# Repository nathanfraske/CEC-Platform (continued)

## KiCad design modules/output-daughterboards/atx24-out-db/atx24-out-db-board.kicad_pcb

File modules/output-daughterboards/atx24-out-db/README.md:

# 24-pin ATX output daughterboard — BETA-1

Passive connector-daughterboard for the 24-pin ATX module's OUTPUT side, per
spec **§2.8 v1.4.0** (`CEC-Platform-Ground-Truth-Spec.md`) and the owner
ruling `docs/standard-tier-review/SYNTHESIS-beta-plan.md` §D-5a. Mates with
the main board's `TB1`–`TB9` Keystone 3586 universal blade clips (TB symbols
exist in `modules/atx-24pin-rev3`'s **schematic**, commit `b76a62a`; **no
clip placement exists on any main-board PCB yet** — this board's tab grid is
the authoritative mating drawing, see "Keying") and reproduces the full
24-circuit ATX output pin map for a bare pigtail or a future MODDIY-class
vertical header. **No active or passive components** — connector bodies and
fan-out copper only, per the ratified "no components beyond the connector
body and its fan-out copper" text.

> **ITERATION 7 (2026-07-06, owner-ratified) — READ FIRST, supersedes the
> iteration-5 numbers below where they differ.** Main-board mate changed:
> Keystone **3557 clip → TE 63969-1 FASTON .250 PCB RECEPTACLE** (vertical/
> top entry; the DESIGNED mate for the 63951-1 blade — rev-E dwg note 3
> puts our 0.81 mm thickness at its design centre, retiring the
> 27%-over-centre fit item; 22.9 A @ 30 °C rise per TE 108-1706; 63968-1 =
> same-land low-insertion-force fallback; LCSC C2961150, stock ~5 =
> restock watch, DigiKey depth). **ORIENTATION (owner requirement, proven
> from `lib/datasheets/TE_63969_customer_drawing_revE.pdf` and
> checker-asserted):** the receptacle's two Ø1.40 holes at 5.08 mm pitch
> run **perpendicular to the row**, along the descending blade's plane —
> plan-congruent with the blade's own leg holes; the blade's bottom edge
> enters the slot edge-wise. Along-row footprint is therefore only the
> receptacle's ~3.7 mm across-thickness depth (UN-DIMENSIONED on rev E —
> **depth ≤ 4.0 mm is the #1 sample-gate item; above it, atx24 falls back
> to a 6.3 pitch**): pitch floor 3.7 + 0.5 = **4.2 mm**; pitches now
> **atx24 4.2 / eps 4.7 / pcie 5.2**. Joint counts re-ratified at
> 22.9 A/125% (18.32 A allowable per joint): **atx24 10 tabs** (3V3 gains a
> second joint at 24.0 A basis; GND ×4 = 18.0 A/joint = 127% hairline,
> surfaced), **eps holds 6/cable** (17.33 A = 132%), **pcie 6/cable**
> (3/polarity; 2/polarity was 19.5 A = 117% FAIL). Boards: **atx24 61.0 ×
> 21.4, eps 28.5 × 20.0, pcie 31.0 × 20.0 mm** (pcie GROWS — the +2
> ratified joints outweigh its pitch win; honest number). Seating: float
> 12.41 mm unchanged; the 8.38 mm receptacle top is cleared by **4.03 mm**;
> detent-hole engagement at nominal float is NOT established (retention may
> be spring-friction only — sample item, with gang insertion force). Full
> record: `docs/standard-tier-review/blade-fit-check-2026-07-04.md`
> **addenda 6–7**.

> **ITERATION 5 (2026-07-05, owner) — READ FIRST, supersedes the iteration-4
> numbers below where they differ.** Main-board clip part changed: Keystone
> **3586 (SMD) → 3557 bare top-entry clip** (THT, UL 30 A @ 500 V AC; the
> "3557-2" this repo vendored earlier is the 2-in-1 HOUSED holder, a
> different product — naming corrected; 3586 stays vendored as the SMD
> fallback). Clip rotated slot-perpendicular-to-wall; its **leg pair runs
> ALONG the row** (verified from the catalog mounting details — this
> contradicts the leg-parallel-to-jaw assumption and caps the win): pitch
> floor = 3.4 leg pitch + 2.4 pad + 0.5 solder web = **6.3 mm**, pitches now
> **atx24 6.3 / eps 6.7 / pcie 7.2** (keying margins 1.00/0.75/1.35, teeth
> re-verified). Boards: **atx24 69.5 × 21.4, eps 38.5 × 20.0, pcie 26.6 ×
> 20.0 mm**. Seating: uniform 4.34 mm leg row, float 12.41 mm at 1.0 mm tip
> clearance; the taller 10.2 mm clip's top is cleared by 2.21 mm; engagement
> now spans the clip's full interior. atx24 also swaps its signal stub: the
> 2×5 header is RETIRED for a **1×4 right-angle blind-mate pin header**
> (long-tail Dupont class, pins down past the edge parallel to the blades,
> single-motion drop-in; NEW pin map 1=−12V, 2=PS_ON#, 3=PWR_OK, 4=GND) plus
> **six DNP sense-return pads SR1–SR6** (OQ-88 provision form only). #1
> fit-check item: the 0.81 mm FASTON tab is ~27% over the clip's 0.64 mm
> fuse-blade design centre (inside the published .020–.032 acceptance, at
> its ceiling — stiffer grip expected, sample-gated). Full record:
> `docs/standard-tier-review/blade-fit-check-2026-07-04.md` **addendum 5**.

DRAFT (no fab yet — the OQ-86 physical fit-check sample gate is still open).

## Posture — vertical card, tabs blade-DOWN (owner sketch, 2026-07-05)

This board is a small vertical card standing perpendicular to the main board
(owner ruling 2026-07-04/05, unchanged). The connector form went through
three same-day iterations on 2026-07-05 and is settled by the **owner's
sketch** (the final ruling; the two earlier forms — TE 63849-1
straight-tab/side-entry, then a mis-modeled "blade hangs past the edge
in-plane" reading of the 63951-1 — are retired, record in
`docs/standard-tier-review/blade-fit-check-2026-07-04.md` addendum 3):

The tabs are **TE 63951-1** (RIGHT-ANGLE FASTON .250 — "the blade that has
the 90 degree rotation in it," owner). The part is a flat in-plane **L
stamping**: the blade runs along the leg-pitch axis past the blade-side leg,
standing **2.54–8.89 mm off its seating face** (TE dwg C=63951 rev L2,
`lib/datasheets/TE_63951-1.pdf`). Mounted per the sketch: the two legs go
**horizontally** through this board's face, the 5.08 mm leg pitch runs
**vertically** (legs stacked one above the other), and the blade therefore
points **straight down**, descending past this board's bottom edge at the
2.54–8.89 mm Z-standoff — *"It needs to align vertically so it can actually
point down and slot into the clip."* The whole assembly drops vertically;
each blade enters its main-board Keystone 3586 clip's **top-entry** jaws
broadside (the clip's native auto-blade-fuse mode, Keystone dwg 3586). The
board's own bottom edge **floats clear of the main board** — *"the TAB does
the reaching down, not the board"* — no board material or copper crosses
Edge.Cuts; only the tab's off-board descender passes below the edge level,
offset from the board plane with no conflict.

**Board axes**: X = length (FREE dimension, minimized opportunistically);
Y = height. **The ≤15 mm height cap is EXPLICITLY RELAXED by the owner for
the iteration-4 compact form** (owner follow-up on the 145 mm iteration-3
board: *"Good lord those are long, can the agent stack the blades right
next to each other and put them below the pinout? That should tell us how
tall these are really going to be"*) — the deliverable is the honest
minimum height of the two-band stack.

**Measured final size**: **69.5 × 21.4 mm** (length × height). The tab row
returned BELOW the field (two-band stack: field + corridor on top, packed
tab row underneath), halving the length (145.1 → 72.8 mm) at a true height
cost of 13.6 → 21.4 mm. Height decomposition (all measured constants):
0.4 top margin + 10.2 field + 0.1 gap + 2.25 corridor (4 In2 lanes) +
0.3 lane-to-pad clearance + 7.58 tab pad band (2 × 3.79) + 0.55 edge
margin. Length is now tab-row-driven (9 × 8.4 mm + margins ≈ 73, just over
the field+header band's ~68).

## Mating geometry / seating model (iteration-4 numbers)

All numbers from `scripts/gen-output-daughterboard.py seating_report()` and
the two vendored drawings; the seating invariant is now the leg-row height
ABOVE THE BOTTOM EDGE, **uniform across all three families** (the tab band
is the lowest thing on every board; asserted by the check script):

- **Leg row** (leg-pair midpoint): **4.34 mm above the bottom edge**
  (= 3.79 pad extent + 0.55 edge margin; the lower pad's copper clears the
  board's 0.5 mm copper-to-edge constraint by 0.05 mm — sized off the
  iteration-3 `copper_edge_clearance` lesson, asserted by the checker).
- **Blade standoff** (unchanged): descender hangs 2.54–8.89 mm off the
  front face; main-board **clip slot centreline at 5.72 mm** from the wall
  plane, slot axis PERPENDICULAR to the wall line; blade width 6.35 mm vs.
  the clip's rated ≤6.4 mm accepted-tab range; slot opening 1.57 mm vs.
  0.77–0.83 mm blade thickness — ~2× clearance.
- **Descender reach**: blade tip 15.75 mm below the leg row (drawing-derived
  chain dim, flagged in the footprint descr) → the tip descends **11.41 mm
  below the bottom-edge level** — uniform across families now, off-board at
  the Z-standoff.
- **Seating**: the board **cannot and does not edge-rest** — it floats,
  hanging on the clip grip (+ chassis strain relief, OQ-87). At the
  recommended **1.0 mm tip clearance** above the main-board surface (hard
  stop ≈0.4–0.5 mm when the tip meets the clip's own SMT base metal), the
  bottom edge floats **12.41 mm** above the main board — now UNIFORM across
  all three families (the invariant moved from iteration-3's "uniform
  top-edge height" to "uniform float" when the tab band became
  bottom-pinned); this board's top edge sits **33.8 mm** above the main
  board (eps/pcie: 32.4 mm). The compact form trades assembly stack height
  for board length — reported, not hidden. **Engagement** unchanged: the
  blade spans the clip's full 7.16 mm interior from the tip clearance up
  and protrudes fuse-like above the clip top. Legs protrude 2.21 mm out
  the back face (3.81 mm legs − 1.6 mm board); keep that clear behind the
  wall.

## Mounting / retention — no mounting holes (owner directive, 2026-07-05)

Earlier drafts of this pass carried 4× M3 corner mounts; the owner cut them:
*"they don't need a ton of mounting holes either... that can probably go
away."* Retention is instead:
1. The Keystone 3586 clip's own **high insertion force** — a deliberate
   **feature**, not a shortfall, per the owner's 2026-07-04 ruling on this
   connector family: these joints are not meant for casual swapping, and
   mis-seat/pull-out (which hardware would be there to prevent) is exactly
   the failure a stiff joint rejects.
2. **Chassis strain relief** on the cable/assembly side (spec §2.8 v1.4.0);
   OQ-87 still owns the numeric pull-force/flex-cycle spec for that
   interface.
No footprint or BOM line changed because of this — mounts were never a
schematic/BOM part on this generator (PCB-only mechanical footprints), so
removing them only touched the PCB placement code.

## Tab map (9 joints, TE 63951-1 / LCSC C591344)

| Ref | Net | ATX pins bundled | Matches main-board clip |
|---|---|---|---|
| J10 | +12V | 10, 11 | TB1 |
| J11 | +5V | (shares +5V net with J12) | TB2 |
| J12 | +5V | 4, 6, 21, 22, 23 | TB3 |
| J13 | +3V3 | 1, 2, 12, 13 | TB4 |
| J14 | +5VSB | 9 | TB5 |
| J15–J18 | GND | 3, 5, 7, 15, 17, 18, 19, 24 | TB6–TB9 |

Joint count and per-rail split (12V×1, 5V×2, 3.3V×1, 5VSB×1, GND×4) are the
spec-ratified §2.8 v1.4.0 numbers, and the tab ORDER (12V, 5V, 5V, 3.3V,
5VSB, GND×4) matches the already-built main board's `TB1`–`TB9` net sequence
1:1 — verified against `modules/atx-24pin-rev3/README.md`.

## Signal header (J20, 2×5 2.54 mm, `cec:CEC_CONN_2x5`)

Pin order matches the main board's `J_SIG` (same commit) exactly, so a
mating cable/header is not left to guess a 1↔2 swap:

| Pin | Net | Note |
|---|---|---|
| 1 | PS_ON# | |
| 2 | PWR_OK | |
| 3 | −12V | |
| 4 | GND | local reference |
| 5–10 | reserved | no-connect; sense-return provision (OQ-88), unpopulated |

No 5VSB-sense/remote-sense net exists on the main board's signal set today
(verified against the current netlist per that board's own README), so none
is carried here either.

## Output field (J1, `cec-Connector_Generic:ATX24_Daughterboard_Field_P4.20mm`)

Bare THT solder field, 24 positions, 2×12 @ 4.20 mm pitch / 5.5 mm row —
geometry measured off the vendored, verified Molex Mini-Fit Jr 5569-24A1
land (`lib/vendor/Connector_Molex.pretty`), same pitch family the study's §4
recommends for exactly this field. Reuses the platform's own `cec:CEC_ATX_24`
symbol (same pin names/map as J3 on the 24-pin module) so the electrical
identity is inherited verbatim; only the footprint differs — a bare pad
field, no male-header shroud. 20 of the 24 positions are power-class (1.8 mm
drill / 2.7×3.7 mm oval, the real Molex land, 16 AWG-class); the 4 non-power
ATX circuits (pin 8 PWR_OK, pin 14 −12V, pin 16 PS_ON#, pin 20 NC/reserved)
are downsized to 1.4 mm drill / 2.6 mm round (18 AWG-class, matching the TE
tab's own leg size).

**Population options** (same field serves all three, per the study §4 "one
field, two/three uses"):
1. **Bare pigtail** (default) — hand-solder 16 AWG (power) / 18 AWG (signal)
   wire directly into the field.
2. **MODDIY-class vertical female header** — dimensionally compatible
   (4.20 mm pitch, same "Molex 5557/5559 family" pitch the part claims), but
   **NOT placed here**: no MODDIY footprint is vendored in this library (no
   manufacturer name / MPN / datasheet — OQ-88's provenance gap), so nothing
   is invented. On the standing-board posture the header's own pins point
   horizontally (same direction as the tabs), so — unlike an earlier,
   since-corrected concern about a parallel-mezzanine framing — there is no
   height-budget conflict with a vertical header option here; population
   stays an owner decision pending the physical fit check (OQ-86/88).
3. **Sellable daughterboard-plus-extension assembly** — same holes, wire
   soldered in with a chassis-anchored strain-relief bar, terminating in a
   standard female housing (OQ-89, SKU TBD). Wire dress runs parallel to the
   main board (the natural consequence of the field's pins exiting
   perpendicular to a *standing* board — i.e. horizontally).

## Keying

**Single row of 9 tabs at 8.9 mm pitch** (mm centre-to-centre), net order
unchanged from the original design (12V, 5V, 5V, 3.3V, 5VSB, GND×4) — see
the tab map above. Under the sketch model the pitch floor is no longer the
tab body at all (each tab is only ~0.84 mm thin along the row, stamping
plane perpendicular to the face; its 2.5 mm pads are its widest row-axis
feature → tab-to-tab pad gap 5.9 mm — trivially clear). The binding floor
is the **main-board clip row**: the Keystone 3586 rotated per the sketch
(slot axis perpendicular to the wall) presents its narrow dimension along
the row — 3.81 mm body / 3.82 mm courtyard (measured off the vendored
footprint; Keystone dwg 3586 `.150 in`) and — the real driver — a
**6.60 mm SMD pad span**. **Pitch floor = 6.60 + 0.50 stated adjacent-clip
solder/paste clearance = 7.10 mm** (iteration-4 packed row, owner: "stack
the blades right next to each other"). This board sits at **8.4 mm** —
above the floor for a ROUTING reason, not slack: 8.4 = 4 × 2.1 mm, the
field-stub lattice period (4.2 mm ATX columns + the +2.1 mm dodge), and
`pcb_placement()` grid-aligns the row's x0 to lattice + 1.05 mm, so every
tab stub/via in the shared corridor X-range clears every field stub/via by
≥1.05 mm against a ~0.7 mm conflict radius (at any non-multiple pitch the
9 tabs' lattice offsets provably sweep the full 2.1 mm cycle and some tab
always lands in conflict). At 8.4 mm: **4.58 mm clip body gap, 1.80 mm pad
gap** — asserted with printed numbers by `check_output_daughterboards.py`
§3b.

**The real safety property is proved, not assumed.**
`scripts/check_output_daughterboards.py` computes every family's tab-centre
list from its own `pcb_placement()` (the exact coordinates on the committed
board) and, for every ORDERED pair of families, searches all 4 rotations
(0/90/180/270°) × every candidate translation for a rigid mapping that seats
one family's whole tab set onto a subset of another's, within 0.5 mm
(bipartite exact-match, not a coincidence heuristic) — see that script for
the algorithm. All 6 ordered pairs come back "cannot seat" — **re-proved at
the iteration-4 packed pitches (8.4/7.6/7.1)**, whose keying margins are
(G/2)×Δpitch: pcie-in-eps 0.75 mm, pcie-in-atx24 1.95 mm, eps-in-atx24
2.00 mm — all ≥1.5× the 0.5 mm tolerance, so **pitch differentiation
survives at the packed floor and no pattern keying (offset tab /
asymmetric skip) was needed**. The historic failure mode stays live in the
checker's teeth: an earlier set (8.6/8.3/8.2) MEASURABLY seated PCIe's 4
tabs inside EPS's grid at only 0.15 mm end error, and a sabotaged 7.2 mm
EPS pitch (Δ0.1 from pcie's 7.1) was re-verified this pass to make the
proof correctly FAIL. See `scripts/gen-output-daughterboard.py`'s
`TAB_PITCH` comment for the full floor + delta math. **This
daughterboard's tab grid is the authoritative main-board mating drawing** —
the four main boards carry TB clip SYMBOLS in their schematics only (no PCB
placement exists on this branch), so the future main-board clip-placement
pass mirrors these exact X positions, the rotated-clip orientation, and the
5.72 mm slot-centreline standoff from the wall plane.

**Dual-face tabs**: evaluated and REJECTED under the earlier flat-tab model
(cross-face interleaving relieved only pad-to-pad clearance, ~11 %, not the
assumed ~50 % — full math retained in this section's git history). Under
the sketch model the question is moot a fortiori: the row pitch is
clip-limited and keying-limited, not tab-body-limited (each tab is ~0.84 mm
thin along the row), so a second face would buy nothing. Single-face,
single-row stands.

## Layer stack / routing

**4-layer** (F.Cu / In1.Cu / In2.Cu / B.Cu, 2 oz outer / 1 oz inner — the
platform's own interposer convention). GND floods **In1.Cu alone**, a
single full-board plane (the largest, most-scattered net; GND tabs and GND
field pins connect through it with zero explicit tracks). Of the remaining
7 nets, only **4 are real multi-point busses** — +12V, +5V, +3V3, +5VSB
(several field pins, one or two tabs each) — and only THOSE get a lane. The
other 3 (−12V, PWR_OK, PS_ON#) are a plain 2-terminal net apiece (exactly
one field pin to the matching `J20` header pin, no tab at all,
netlist-verified), so they route as direct point-to-point tracks with no
lane at all — see the two design notes below.

**The 4 BUS lanes live in a short CORRIDOR** below the field's bottom row,
on **In2.Cu only** — 4 thin zones (0.3 mm wide, 0.65 mm pitch) spanning the
full board width. Each bus field-pin runs a 0.5 mm F.Cu stub down to its
own lane + a 0.3/0.5 mm via (smaller than this platform's usual 0.5/0.9 mm
power via — the 0.65 mm slot pitch cannot safely hold a 0.9 mm via without
adjacent slots' vias overlapping). Each rail TAB — now in the packed row
BELOW the corridor (iteration-4 two-band stack), legs stacked vertically —
bridges its two leg pads (both numbered "1" but with no internal copper
between them in the footprint) with a vertical 0.5 mm F.Cu track, plus an
up-stub from the UPPER leg into its own lane + the same 0.3/0.5 mm via.
The tab row shares the corridor's X-range with the field's own stubs/vias,
which is exactly what the 8.4 mm grid-aligned pitch solves (see "Keying"):
every tab stub/via sits 1.05 mm off the field-stub lattice. The tab pads'
own In2 anti-pads stay 0.3 mm clear of the deepest lane band by placement
(`_LANE_PAD_CLR` — deliberately above the 0.2 mm zone clearance so the
fill never sits at exact tangency with a pad anti-pad); the via sits at
its own lane's centreline, clearing the 0.65 mm-pitch neighbours by the
same measured 0.25 mm the field vias rely on. The board's bottom margin
below the tab pads is 0.55 mm (0.5 mm board copper-to-edge constraint +
0.05 slack — the iteration-3 `copper_edge_clearance` lesson applied up
front), which is what the 21.4 mm height lands on.

**DESIGN NOTE — a two-layer lane split does NOT help here, though it looks
like it should** (a first pass built one, then reverted it once DRC caught
the result). Splitting the 4 (or originally, all 7) lanes across In2.Cu
*and* B.Cu, thinking two layers halve the stack depth, is unsafe for a
zone this thin: a via is a THROUGH feature, so a B.Cu-target via also
crosses In2.Cu at that (x,y), and KiCad's `ZONE_FILLER` auto-clears
(anti-pads) it there — normally harmless (exactly how a signal via safely
crosses a GND plane everywhere on this platform) *only* because a plane is
wide in both directions and copper can route around the hole. A 0.3 mm-tall
lane has no "around": a via whose keepout diameter (~0.9 mm here) exceeds
the lane's own height clears its FULL height at that one X, severing it
into two islands — measured as a real `unconnected_items` DRC hit between
two ends of what should obviously be one zone. Offsetting the two layers'
Y by half a pitch does not fix it either: the safe stand-off a via needs
from a foreign-LAYER lane it merely passes near
(`via_keepout_radius + lane_half_height + min_width`, ≈0.8 mm here) is the
same separation the lanes already need from EACH OTHER on one layer — two
layers buy nothing once every slot carries a via. The actual fix was fewer
lanes (drop the 3 point-to-point signals out of the scheme entirely), not
more layers.

**The 3 point-to-point signals (−12V/PWR_OK/PS_ON#) route on B.Cu**,
deliberately NOT F.Cu: the bus field-pins' dodge-then-descend stubs (below)
are on F.Cu and physically transit this same row-gap band on their way to
the corridor, at up to 12 different X's, so putting the point-to-point
runs on the otherwise-empty B.Cu avoids that whole family of crossings in
one move. No via is needed at either end (both the field pins and the
header pins are through-hole). The three runs still share one layer with
each other, so each gets its own dedicated Y inside the field's row-gap
(0.42 mm steps, a 0.2 mm track — thinner than the platform-default 0.4 mm,
because the safe row-gap window is only ~1.1 mm wide once the 0.25 mm
GND-class clearance and each pad's own 1.85 mm half-height are accounted
for), assigned by which row each signal approaches from so no two runs'
occupied (X, Y) actually coincide — worked out and commented in
`route_atx24()`, `scripts/gen-output-daughterboard.py`.

**Row-conflict fan-out rule** (why some bus field-pin stubs jog sideways):
the real ATX-24 pinout puts row0 (pins 1–12) and row1 (pins 13–24) on the
*same* 12 X-columns, so a straight vertical stub from a row0 pin can run
directly into a *different-net* row1 pad below it. Fixed by a **permanent
+2.1 mm (half the 4.20 mm pitch) sideways offset** on exactly the row0 pins
whose column-mate differs — landing dead-centre in the gap between two
adjacent pad columns (~0.75 mm clear of both neighbours) — taken for the
pin's *entire* descent (never jogged back), which also keeps every column's
own stub on a unique X for its whole length. Row1 pins and same-net columns
route straight down natively.

Field-pin currents here are modest (24-pin design basis: 6 A/circuit, ATX
bar) — 0.5 mm 2 oz stub tracks are comfortably inside that per-pin figure;
the per-rail AGGREGATE current (up to ~30 A on the 5V rail, per the study's
§1 margin table) is what the **9 blade-clip joints on the main board** are
sized for, not this daughterboard's own individual per-pin fan-out traces.
Verified DRC-clean (see below).

## Electrothermal sanity — PENDING (W-item, not wired this pass)

The repo's `cec_synth_pipeline.physics.electrothermal_solve` (IPC-2221 Picard
solver) is not parametrized for this board's "per-pin stub + thin lane"
topology; wiring it up is not cheap within this pass's scope. Hand sanity
only: 0.5 mm/2 oz external-layer traces at a 10 °C rise carry roughly 2–3 A
by the standard IPC-2221 external-trace curve — comfortably above the
~6 A/circuit-shared, sub-amp-per-stub currents these individual field-pin
fan-out traces actually see (the real per-rail current rides the 9 blade
joints, sized separately per the study). Flagged as a **pending W-item**:
run the real solver once it is generalized to this topology, before treating
this board as production-ready.

> **RESULT (2026-07-06, blade-interconnect thermal audit — the W-item above
> was executed): FAIL.** The four In2 bus lanes (0.3 mm × 1 oz) carry the
> full per-rail aggregates and are fusing-class at the design basis:
> DC-IR field solve = +5V 384 mV @ 30 A (11.5 W in the lane, J ≈ 2874 A/mm²),
> +12V 817 mV @ 12 A, +3V3 299 mV @ 24 A (9 % of the rail); the 2.5D coupled
> solve runs away (lane fuses). The hand sanity above sized the per-pin
> STUBS but the per-rail AGGREGATE crosses the lane between the tab group
> and the field pins (and ATX permits 6 A/pin, not "sub-amp"). Board fix =
> owner-gated regen (per-rail pour bands à la eps/pcie, or a widened 2 oz
> outer corridor). Full analysis:
> `docs/standard-tier-review/blade-interconnect-thermal-2026-07-06.md` (F1).

## Sense-return provision

Per spec §2.8 v1.4.0 / OQ-88: a zero-component sense-return contact (a
downstream voltage tap per sensed rail, feeding a main-board resistor divider
and spare ADC — mirrors Hub Standard's `MAIN_5V_SENSE`/`5VSB_SENSE` pattern)
is a candidate designed-in monitor for this joint's fretting-corrosion
wear-out mode. **Not decided** whether it ships, when, or at what
granularity — this board **provisions** for it only: 6 of the J20 header's
10 positions are reserved/no-connect, physically available for a future
sense-return tap without a board respin. No components are added here.

## Verification (this pass — 2026-07-05 iteration-4 compact two-band layout)

- ERC: 0 errors (5 benign `lib_symbol_mismatch` warnings, the same
  documented-benign class every generated schematic in this repo produces).
- Static connectivity audit (`scripts/audit-sch.py`): clean.
- DRC: **0 violations at error severity, 0 unconnected** (`kicad-cli pcb drc
  --severity-error`, and every `unconnected_items` slot is empty — the real
  gate `check_output_daughterboards.py` enforces). At full (all-severity)
  verbosity: 25 hits — 4 `silk_overlap` + 20 `silk_over_copper` (the
  documented-benign class) + 1 `silk_edge_clearance` (a single Value text
  near the bottom edge on the packed board — warning severity, no copper
  impact, same benign class as the platform's other boards carry). The
  iteration-3 `copper_edge_clearance` lesson (deepest copper vs the
  board's 0.5 mm edge constraint) is designed in up front this pass
  (`_TAB_EDGE_MARGIN` 0.55) — zero copper-edge hits on first regeneration.
- `scripts/check_output_daughterboards.py`: **all checks pass**, including
  the updated sketch-model checks (every tab rot 0 with legs stacked
  vertically at (0, ±2.54) re-parsed from the footprint file; the NEW
  uniform seating invariant — leg row 4.34 mm above the bottom edge on all
  three boards, lower pad clearing the 0.5 mm copper-to-edge constraint)
  and the §3b clip-fit assertions recomputed at the packed pitches (floors:
  0.5 mm pad gap = the stated solder clearance; 3.0 mm body gap). The
  geometric no-subset-seating proof re-ran at 8.4/7.6/7.1. Teeth
  re-verified at the packed floor: a sabotaged 7.2 mm EPS pitch (Δ0.1 from
  pcie's 7.1) makes the proof correctly FAIL (PCIe seats as a subset) —
  the same failure mode as the historic 8.3/8.2 incident.
- Netlist-verified: every one of the 9 tabs lands on its mapped ATX rail;
  every header pin lands on its mapped signal/GND/reserved net; the field's
  24 positions reproduce the standard ATX-24 map exactly (pin 20 = NC).
  Net-group identity vs. the pre-rework baseline confirmed (15→15 groups,
  0 missing/extra/renamed).

## Library assets used / added this pass

- **`cec-vendor:TE_63951-1_FASTON_Tab` / `cec-Connector_Blade:TE_63951-1_FASTON_Tab_250x032_RA_THT`
  (LCSC C591344, in stock, $0.099–$0.164/unit by qty)** — the right-angle
  .250 FASTON tab, footprint REWRITTEN this pass to the true in-plane-L
  geometry (legs at (0, ±2.54) stacked vertically, blade descending +Y past
  the board edge at the 2.54–8.89 mm standoff; thin projection-band
  courtyard/fab incl. the below-edge descender, drawn honestly) from TE's
  own customer drawing C=63951 rev L2 (`lib/datasheets/TE_63951-1.pdf`).
  The pass's first footprint modeled the L wrongly (blade perpendicular to
  the leg row, hanging past the edge in-plane) — retired by the owner's
  sketch; see `docs/standard-tier-review/blade-fit-check-2026-07-04.md`
  addendum 3.
- `cec-vendor:TE_63849-1_FASTON_Tab` / `cec-Connector_Blade:TE_63849-1_FASTON_Tab_250x032_THT`
  — pre-existing, LCSC C86469, **unreferenced by this generator** (left
  vendored; harmless).
- `cec:CEC_ATX_24` (pre-existing, reused verbatim for the field connector's electrical identity).
- `cec:CEC_CONN_2x5` + `cec-Connector_PinHeader_2.54mm:PinHeader_2x05_P2.54mm_Vertical` (pre-existing from the main-board task; this project's own library-asset pass independently reproduced byte-identical geometry).
- `cec-Connector_Generic:ATX24_Daughterboard_Field_P4.20mm` (this family's
  own field footprint; its Y-margin was tightened in an earlier pass —
  `scripts/gen-daughterboard-libassets.py`'s `solder_field()` now uses actual
  pad half-height instead of half the row pitch, dropping the field's own
  courtyard height 13.0→10.2 mm, the single biggest lever in fitting this
  board under the height cap — see that script for the reasoning).
  Unchanged this pass.
- No mounting-hole footprint — removed in an earlier pass (owner directive;
  see "Mounting / retention" above). Never a schematic/BOM part on this
  generator, so the BOM is unaffected.

Generator: `scripts/gen-output-daughterboard.py atx24-out-db`.

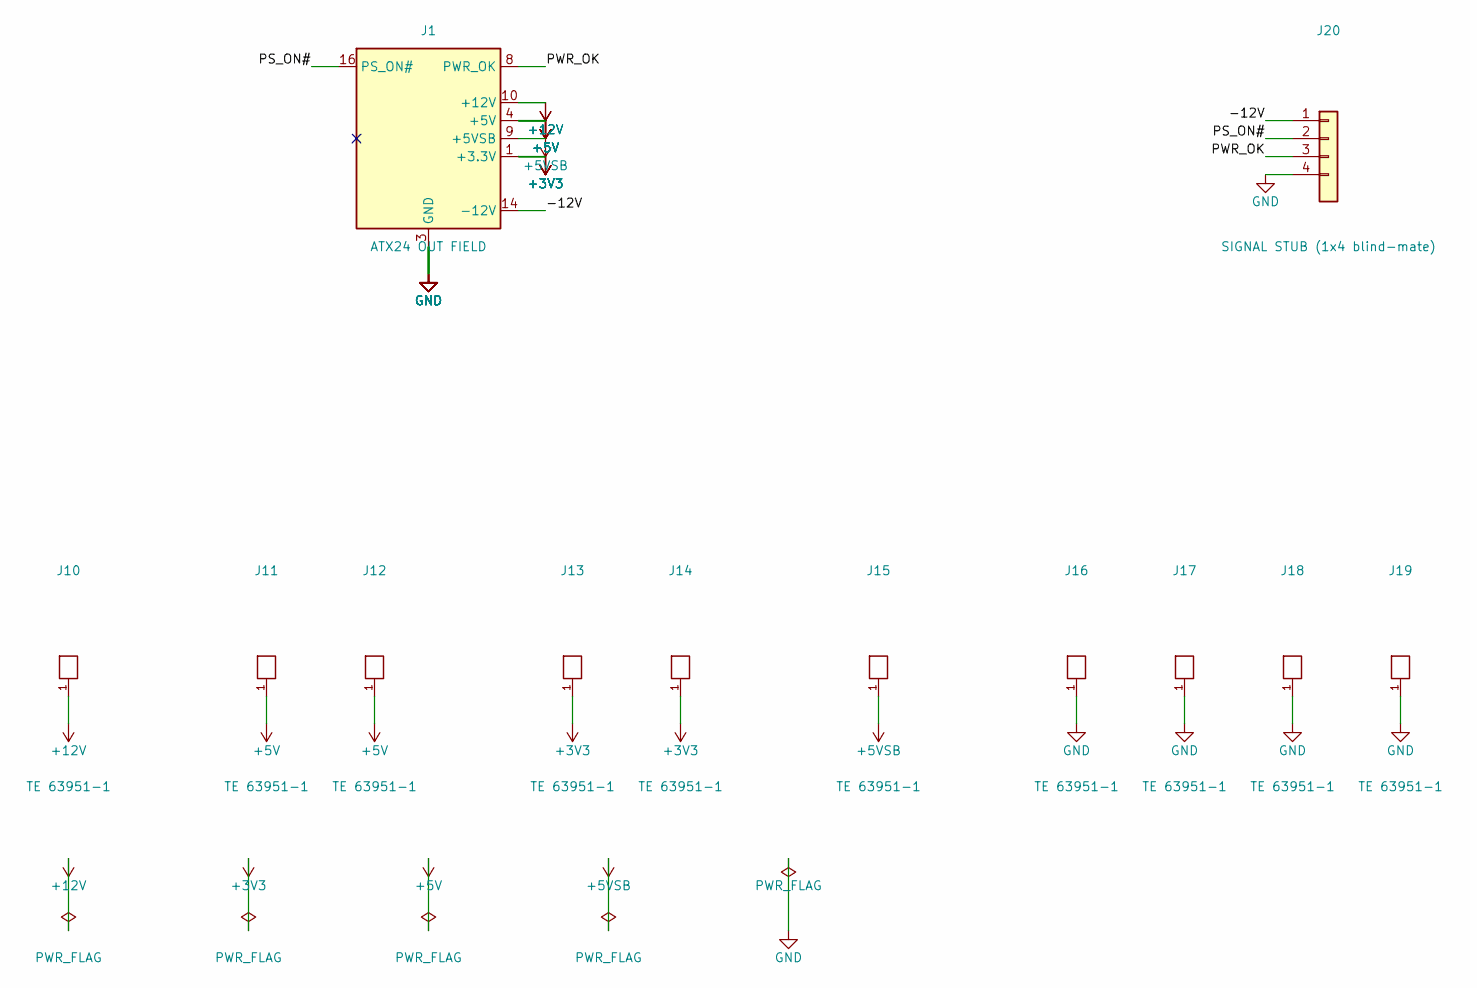
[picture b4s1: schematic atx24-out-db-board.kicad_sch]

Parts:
J1: ATX24 OUT FIELD; ATX24_Daughterboard_Field_P4.20mm
J10, J11, J12, J13, J14, J15, J16, J17, J18, J19: TE 63951-1; TE_63951-1_FASTON_Tab_250x032_RA_THT; MPN 63951-1; LCSC C591344
J20: SIGNAL STUB (1x4 blind-mate); PinHeader_1x04_P2.54mm_Horizontal_LongPin

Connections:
+3V3: J1.1 (+3.3V), J1.2 (+3.3V), J1.12 (+3.3V), J1.13 (+3.3V), J13.1, J14.1
+5V: J1.4 (+5V), J1.6 (+5V), J1.21 (+5V), J1.22 (+5V), J1.23 (+5V), J11.1, J12.1
+5VSB: J1.9 (+5VSB), J15.1
+12V: J1.10 (+12V), J1.11 (+12V), J10.1
/-12V: J1.14 (-12V), J20.1
/PS_ON#: J1.16 (PS_ON#), J20.2
/PWR_OK: J1.8 (PWR_OK), J20.3
GND: J1.3 (GND), J1.5 (GND), J1.7 (GND), J1.15 (GND), J1.17 (GND), J1.18 (GND), J1.19 (GND), J1.24 (GND), J16.1, J17.1, J18.1, J19.1, J20.4

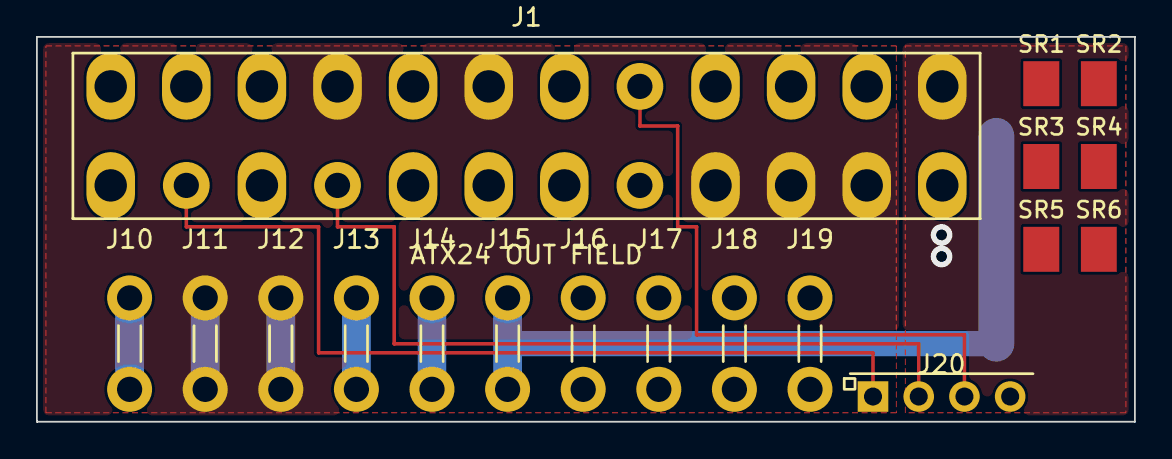
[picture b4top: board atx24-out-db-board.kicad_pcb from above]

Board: 4 copper layers, 61.0 x 21.4 mm, 18 parts (0 on the bottom side), 8 nets.

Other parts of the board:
SR1, SR2, SR3, SR4, SR5, SR6: SR_DNP; CEC_SR_Pad_DNP

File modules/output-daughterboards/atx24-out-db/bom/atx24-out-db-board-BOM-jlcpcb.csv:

"Reference","Value","Footprint","LCSC","MPN","Manufacturer"
"J1","ATX24 OUT FIELD","cec-Connector_Generic:ATX24_Daughterboard_Field_P4.20mm","","","CEC (in-house)"
"J10","TE 63951-1","cec-Connector_Blade:TE_63951-1_FASTON_Tab_250x032_RA_THT","C591344","63951-1","TE Connectivity"
"J11","TE 63951-1","cec-Connector_Blade:TE_63951-1_FASTON_Tab_250x032_RA_THT","C591344","63951-1","TE Connectivity"
"J12","TE 63951-1","cec-Connector_Blade:TE_63951-1_FASTON_Tab_250x032_RA_THT","C591344","63951-1","TE Connectivity"
"J13","TE 63951-1","cec-Connector_Blade:TE_63951-1_FASTON_Tab_250x032_RA_THT","C591344","63951-1","TE Connectivity"
"J14","TE 63951-1","cec-Connector_Blade:TE_63951-1_FASTON_Tab_250x032_RA_THT","C591344","63951-1","TE Connectivity"
"J15","TE 63951-1","cec-Connector_Blade:TE_63951-1_FASTON_Tab_250x032_RA_THT","C591344","63951-1","TE Connectivity"
"J16","TE 63951-1","cec-Connector_Blade:TE_63951-1_FASTON_Tab_250x032_RA_THT","C591344","63951-1","TE Connectivity"
"J17","TE 63951-1","cec-Connector_Blade:TE_63951-1_FASTON_Tab_250x032_RA_THT","C591344","63951-1","TE Connectivity"
"J18","TE 63951-1","cec-Connector_Blade:TE_63951-1_FASTON_Tab_250x032_RA_THT","C591344","63951-1","TE Connectivity"
"J19","TE 63951-1","cec-Connector_Blade:TE_63951-1_FASTON_Tab_250x032_RA_THT","C591344","63951-1","TE Connectivity"
"J20","SIGNAL STUB (1x4 blind-mate)","cec-Connector_PinHeader_2.54mm:PinHeader_1x04_P2.54mm_Horizontal_LongPin","","","generic"

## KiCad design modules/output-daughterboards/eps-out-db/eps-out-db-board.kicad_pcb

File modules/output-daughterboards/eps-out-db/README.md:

# EPS 8-pin output daughterboard (per-cable) — BETA-1

Passive connector-daughterboard for **one** EPS 8-pin cable's OUTPUT side,
per spec **§2.8 v1.4.0** and `docs/standard-tier-review/SYNTHESIS-beta-plan.md`
§D-5a. **One design, instantiated per cable** — the EPS module populates 2
cables, so 2 of these boards are built per module (identical PCB, no
per-cable variant). Mates with the main board's per-cable `TB{n}1`–`TB{n}6`
Keystone 3586 clips (TB symbols exist in `modules/eps-8pin`'s **schematic**,
commit `b76a62a`; **no clip placement exists on any main-board PCB yet** —
this board's tab grid is the authoritative mating drawing, see "Keying").
No active or passive components.

> **ITERATION 7 (2026-07-06, owner-ratified) — READ FIRST, supersedes the
> iteration-5 numbers below where they differ.** Main-board mate changed:
> Keystone **3557 clip → TE 63969-1 FASTON .250 PCB RECEPTACLE** (vertical/
> top entry; the DESIGNED mate for the 63951-1 blade — rev-E dwg note 3
> puts our 0.81 mm thickness at its design centre, retiring the
> 27%-over-centre fit item; 22.9 A @ 30 °C rise per TE 108-1706; 63968-1 =
> same-land low-insertion-force fallback; LCSC C2961150, stock ~5 =
> restock watch, DigiKey depth). **ORIENTATION (owner requirement, proven
> from `lib/datasheets/TE_63969_customer_drawing_revE.pdf` and
> checker-asserted):** the receptacle's two Ø1.40 holes at 5.08 mm pitch
> run **perpendicular to the row**, along the descending blade's plane —
> plan-congruent with the blade's own leg holes; the blade's bottom edge
> enters the slot edge-wise. Along-row footprint is therefore only the
> receptacle's ~3.7 mm across-thickness depth (UN-DIMENSIONED on rev E —
> **depth ≤ 4.0 mm is the #1 sample-gate item; above it, atx24 falls back
> to a 6.3 pitch**): pitch floor 3.7 + 0.5 = **4.2 mm**; pitches now
> **atx24 4.2 / eps 4.7 / pcie 5.2**. Joint counts re-ratified at
> 22.9 A/125% (18.32 A allowable per joint): **atx24 10 tabs** (3V3 gains a
> second joint at 24.0 A basis; GND ×4 = 18.0 A/joint = 127% hairline,
> surfaced), **eps holds 6/cable** (17.33 A = 132%), **pcie 6/cable**
> (3/polarity; 2/polarity was 19.5 A = 117% FAIL). Boards: **atx24 61.0 ×
> 21.4, eps 28.5 × 20.0, pcie 31.0 × 20.0 mm** (pcie GROWS — the +2
> ratified joints outweigh its pitch win; honest number). Seating: float
> 12.41 mm unchanged; the 8.38 mm receptacle top is cleared by **4.03 mm**;
> detent-hole engagement at nominal float is NOT established (retention may
> be spring-friction only — sample item, with gang insertion force). Full
> record: `docs/standard-tier-review/blade-fit-check-2026-07-04.md`
> **addenda 6–7**.

> **ITERATION 5 (2026-07-05, owner) — READ FIRST, supersedes the iteration-4
> numbers below where they differ.** Main-board clip part changed: Keystone
> **3586 (SMD) → 3557 bare top-entry clip** (THT, UL 30 A @ 500 V AC; the
> "3557-2" this repo vendored earlier is the 2-in-1 HOUSED holder, a
> different product — naming corrected; 3586 stays vendored as the SMD
> fallback). Clip rotated slot-perpendicular-to-wall; its **leg pair runs
> ALONG the row** (verified from the catalog mounting details — this
> contradicts the leg-parallel-to-jaw assumption and caps the win): pitch
> floor = 3.4 leg pitch + 2.4 pad + 0.5 solder web = **6.3 mm**, pitches now
> **atx24 6.3 / eps 6.7 / pcie 7.2** (keying margins 1.00/0.75/1.35, teeth
> re-verified). Boards: **atx24 69.5 × 21.4, eps 38.5 × 20.0, pcie 26.6 ×
> 20.0 mm**. Seating: uniform 4.34 mm leg row, float 12.41 mm at 1.0 mm tip
> clearance; the taller 10.2 mm clip's top is cleared by 2.21 mm; engagement
> now spans the clip's full interior. atx24 also swaps its signal stub: the
> 2×5 header is RETIRED for a **1×4 right-angle blind-mate pin header**
> (long-tail Dupont class, pins down past the edge parallel to the blades,
> single-motion drop-in; NEW pin map 1=−12V, 2=PS_ON#, 3=PWR_OK, 4=GND) plus
> **six DNP sense-return pads SR1–SR6** (OQ-88 provision form only). #1
> fit-check item: the 0.81 mm FASTON tab is ~27% over the clip's 0.64 mm
> fuse-blade design centre (inside the published .020–.032 acceptance, at
> its ceiling — stiffer grip expected, sample-gated). Full record:
> `docs/standard-tier-review/blade-fit-check-2026-07-04.md` **addendum 5**.

DRAFT (no fab yet — OQ-86 fit-check sample gate open).

## Posture — vertical card, tabs blade-DOWN (owner sketch, 2026-07-05)

This board is a small vertical card standing perpendicular to the main
board (unchanged). The connector form is settled by the **owner's sketch**
(the third and final same-day 2026-07-05 form — the two earlier ones are
retired, record in `docs/standard-tier-review/blade-fit-check-2026-07-04.md`
addendum 3; full geometry description in `atx24-out-db/README.md`
"Posture", identical here): the 6 **TE 63951-1** right-angle FASTON .250
tabs mount with their two legs **horizontal** through this board's face,
leg pitch (5.08 mm) **vertical** (legs stacked one above the other), so
each in-plane-L blade points **straight down**, descending past this
board's bottom edge at a 2.54–8.89 mm Z-standoff from the face. The whole
board drops vertically; the blades enter the main-board Keystone 3586
clips' **top-entry** jaws broadside, and the board's own bottom edge
**floats clear** of the main board — the tab does the reaching, not the
board. Board axes: X = length (FREE); Y = height — **the ≤15 mm cap is
EXPLICITLY RELAXED by the owner for the iteration-4 compact two-band form**
(see the 24-pin README's "Board axes" for the verbatim follow-up).

**Measured final size**: **38.5 × 20.0 mm** (length × height). Iteration 4
stacks the packed tab row BELOW the field band (owner: "stack the blades
right next to each other and put them below the pinout"), cutting length
67.8 → 43.0 mm at an honest height cost of 11.0 → 20.0 mm. Height
decomposition: 0.4 top margin + 10.2 field + 0.25 band gap + 4.82 tab
top-extent (carrier stub) + 3.79 pad lower half + 0.55 edge margin.
Length is tab-row-driven (6 × 7.6 mm pitch + margins).

## Mating geometry / seating model (iteration-4 numbers)

Same uniform model as the 24-pin board (one seating spec platform-wide,
asserted by `check_output_daughterboards.py`; derivation in that README):

- **Leg row**: **4.34 mm above the bottom edge** (uniform across families —
  the tab band is the lowest thing on every board; lower pad clears the
  0.5 mm copper-to-edge constraint by 0.05 mm, checker-asserted).
- **Blade standoff**: 2.54–8.89 mm off the front face; main-board clip slot
  centreline at **5.72 mm** from the wall plane, slot axis perpendicular
  to the wall line.
- **Descender reach**: blade tip 15.75 mm below the leg row → **11.41 mm
  below this board's bottom-edge level** (off-board at the standoff).
- **Seating**: the board **floats** (cannot edge-rest) — at the recommended
  1.0 mm tip clearance above the main-board surface (hard stop ≈0.4–0.5 mm,
  tip on the clip's own base metal), the bottom edge floats **12.41 mm**
  above the main board (now UNIFORM across families); top edge at
  **32.4 mm** (24-pin: 33.8). Blade engagement spans the clip's full
  7.16 mm interior. Legs protrude 2.21 mm out the back face.

## Mounting / retention — no mounting holes (owner directive, 2026-07-05)

Same ruling and rationale as the 24-pin board (see that README): retention
is the Keystone clip's own high insertion force (a feature, not a
shortfall) plus chassis strain relief on the cable/assembly side (OQ-87
owns the numeric spec). No BOM/schematic impact — mounts were a PCB-only
mechanical footprint on this generator, never a schematic part.

## Tab map (6 joints/cable, TE 63951-1 / LCSC C591344)

| Ref | Net | EPS8 pins bundled |
|---|---|---|
| J10, J11, J12 | GND | 1, 2, 3, 4 |
| J13, J14, J15 | +12V | 5, 6, 7, 8 |

3 contacts/polarity — matches spec §2.8 v1.4.0's ratified EPS joint count
(12 total across the module's 2 cables). Design-basis current: ~13 A/pin
continuous → ~52 A/cable sustained worst case → ~65 A margin target (§1 of
the output-daughterboard study), well inside 3× the Keystone 3586's 30 A
field rating (confirm-soak/thermal-cycle contact-R trend recommended before
BOM lock, OQ-86/88 — not gating).

## Output field (J1, `cec-Connector_Generic:EPS8_Daughterboard_Field_P4.20mm`)

Bare THT solder field, 8 positions, 2×4 @ 4.20 mm pitch / 5.5 mm row — the
real Molex Mini-Fit Jr 5569-08A2 land (measured off
`lib/vendor/Connector_Molex.pretty`). Pin map **1–4 = GND, 5–8 = +12V**,
matching the platform's own corrected EPS pinout convention (see
`CLAUDE.md` "EPS 8-pin power-connector pinout fix"). All 8 positions are
power-class (1.8 mm drill / 2.7×3.7 mm oval, 16 AWG-class) — no signal
circuits on this cable. Reuses the generic `cec:CEC_CONN_2x4` symbol
(unnamed pins; the net map lives in the wiring, not the symbol).

**Population options** — identical menu to the 24-pin board (see that
README for the full text): (1) bare 16 AWG pigtail (default); (2)
MODDIY-class vertical header, dimensionally compatible, **not placed** (no
footprint vendored, OQ-88 provenance gap); (3) sellable
daughterboard-plus-extension assembly (OQ-89).

## Keying

**Single row of 6 tabs at 7.6 mm pitch** (iteration-4 packed row), net
order GND×3 then +12V×3 (matching the tab map above). The pitch floor is
the **main-board clip row**, not the tab (each tab is ~0.84 mm thin along
the row; its 2.5 mm pads → 5.1 mm tab pad gap, trivially clear): the
Keystone 3586 rotated slot-perpendicular-to-wall presents 3.81 mm body /
3.82 mm courtyard and a **6.60 mm SMD pad span** along the row — **floor =
6.60 + 0.50 stated solder clearance = 7.10 mm**. This board sits 0.5 mm
above the floor purely for KEYING (the delta to PCIe's at-floor 7.1 mm
pitch that keeps the no-subset proof green — see below). At 7.6 mm:
**3.78 mm clip body gap, 1.00 mm pad gap** — asserted with printed numbers
by `check_output_daughterboards.py` §3b.

**The real safety property is proved geometrically, not by pitch alone.**
`scripts/check_output_daughterboards.py` takes every family's tab-centre
list straight from `pcb_placement()` (the committed board's own
coordinates) and, for every ORDERED pair, searches all 4 rotations
(0/90/180/270°) × every candidate translation for a rigid whole-set mapping
onto a subset of another family's grid, within 0.5 mm (exact bipartite
match). All 6 ordered pairs (this family vs. both others, both directions)
come back "cannot seat" — **re-proved at the iteration-4 packed pitches
(8.4/7.6/7.1)**. The pitch here (7.6 mm) and PCIe's (7.1 mm) differ by
0.5 mm, giving a (G/2)×Δpitch = 0.75 mm end error at PCIe's G=3 — 1.5× the
0.5 mm tolerance, so pitch differentiation survives at the packed floor and
no pattern keying was needed. The historic failure mode (0.1 mm/step over
3 gaps = 0.15 mm end error → PCIe seated inside this board's grid) stays
live in the checker's teeth: a sabotaged 7.2 mm pitch here was re-verified
this pass to make the proof correctly FAIL. See
`scripts/gen-output-daughterboard.py`'s `TAB_PITCH` comment for the floor +
delta math. **This daughterboard's tab grid is the authoritative main-board
mating drawing** for the EPS per-cable clip pattern (TB clip symbols exist
in the main board's schematic only; the future clip-placement pass mirrors
these X positions, the rotated-clip orientation, and the 5.72 mm
slot-centreline standoff).

**Dual-face tabs**: evaluated and rejected under the earlier flat-tab model
(see the 24-pin README); moot a fortiori under the sketch model — the row
pitch is clip/keying-limited, not tab-body-limited. Single-face, single-row
stands.

## Layer stack / current

**4-layer** (F.Cu / In1.Cu / In2.Cu / B.Cu, 2 oz outer / 1 oz inner) — this
is a **2-net board** (GND, +12V), so unlike the 24-pin board there is no
inter-rail banding problem: **GND floods both inner layers** (In1.Cu +
In2.Cu, matching this platform's own already-built EPS/PCIe cable-power
convention — "two GND inners... 12V lives on the OUTERS",
`scripts/gen-module-pcb.py` `gnd_planes()` docstring) and **+12V floods both
outer layers** (F.Cu + B.Cu). Every field pin and blade tab here is a
through-hole pad by construction (no SMD parts on this board at all), so
each already carries copper on every layer; the real `ZONE_FILLER`
auto-clears around every foreign-net pad within a flood's outline and
auto-connects to every same-net pad — **no explicit tracks/vias are needed
at all** for a genuine 2-net board, which is why 2-layer was NOT chosen
instead: doubling the copper thickness on both rails via full F+B and
In1+In2 pairing (four total flooded layers across two nets) directly buys
current margin on the ~65 A/cable target the 2-layer alternative would have
to fight for with much thinner single-layer copper.

## Electrothermal sanity — not needed as a solver run

Both nets are full-board floods on doubled layer pairs with no thin
fan-out geometry to check (no per-pin stub traces exist on this board —
see above); the governing current-capacity question is the **blade-clip
joint** itself (OQ-86's recommended confirm-soak/thermal-cycle bench), not
this board's own copper. Noted, not treated as a gap.

> **CORRECTION (2026-07-06, blade-interconnect thermal audit): the claim
> above is falsified — the solver run WAS needed.** The copper has no thin
> neck (correct), but at the 52 A worst-case basis the board dissipates
> ~2.75 W on ~11 cm² of still air: the 2.5D coupled solve gives
> **dT 216.7 °C** in the enclosed/no-sink posture vs the 30 °C-rise policy —
> a board-LEVEL dissipation red, not a neck. Unmodelled conduction sinks
> (blades → main board, pigtail copper, chassis strain relief) are large
> and the basis is worst-case (dT ~ I²: at half current ~54–71 °C class),
> so this is a gate red pending the OQ-86 thermal-soak datum, not a
> fusing defect. See
> `docs/standard-tier-review/blade-interconnect-thermal-2026-07-06.md` (F2).

## Sense-return provision

Not provisioned on this board (no signal header exists here, unlike the
24-pin board — EPS carries only GND/+12V). If OQ-88's sense-return decision
lands "yes" for EPS, it needs a small signal-tab addition in a future
revision; not a silent gap, just genuinely absent today.

## Verification (this pass — 2026-07-05 iteration-4 compact two-band layout)

- ERC: 0 errors (2 benign `lib_symbol_mismatch` warnings).
- Static connectivity audit: clean.
- DRC: **0 errors, 0 unconnected** (`kicad-cli pcb drc --severity-error`).
  At full verbosity: 17 hits, ALL cosmetic silk (5 `silk_overlap` +
  12 `silk_over_copper` — the documented-benign class; silk counts rose
  with the denser two-band stack, no copper impact).
- `scripts/check_output_daughterboards.py`: all checks pass, including the
  updated sketch-model checks (tab rot 0 / legs vertical / the NEW uniform
  4.34 mm leg-row-above-edge seating invariant / clip-row gaps recomputed
  at the packed pitches) and the geometric no-subset-seating proof re-run
  at 8.4/7.6/7.1 (teeth re-verified at the floor via a sabotaged 7.2 mm
  pitch — see the 24-pin README).
- Netlist-verified: all 6 tabs land on their mapped rail; the field's 8
  positions reproduce the platform's corrected EPS8 pinout exactly.
  Net-group identity vs. the pre-rework baseline confirmed (2→2 groups).

## Library assets used

- **`cec-vendor:TE_63951-1_FASTON_Tab` / `cec-Connector_Blade:TE_63951-1_FASTON_Tab_250x032_RA_THT`
  (LCSC C591344, in stock, $0.099–$0.164/unit by qty)** — right-angle .250
  FASTON tab, footprint REWRITTEN this pass to the true in-plane-L geometry
  (legs stacked vertically at (0, ±2.54), blade descending +Y at the
  2.54–8.89 mm standoff) from TE dwg C=63951 rev L2
  (`lib/datasheets/TE_63951-1.pdf`); see the blade-fit-check addendum 3 for
  the retired interim model.
- `cec-vendor:TE_63849-1_FASTON_Tab` / `cec-Connector_Blade:TE_63849-1_FASTON_Tab_250x032_THT`
  — pre-existing, LCSC C86469, unreferenced by this generator (left
  vendored; harmless).
- `cec:CEC_CONN_2x4` (pre-existing generic connector symbol).
- `cec-Connector_Generic:EPS8_Daughterboard_Field_P4.20mm` — tightened its
  Y-margin in an earlier pass (pad half-height instead of half the row
  pitch, `scripts/gen-daughterboard-libassets.py`), dropping its own
  courtyard height 13.0→10.2 mm; the single biggest lever in clearing the
  height cap. Unchanged this pass.
- No mounting-hole footprint — removed in an earlier pass (owner directive;
  see "Mounting / retention" above). Never a schematic/BOM part on this
  generator, so the BOM is unaffected.

Generator: `scripts/gen-output-daughterboard.py eps-out-db`.

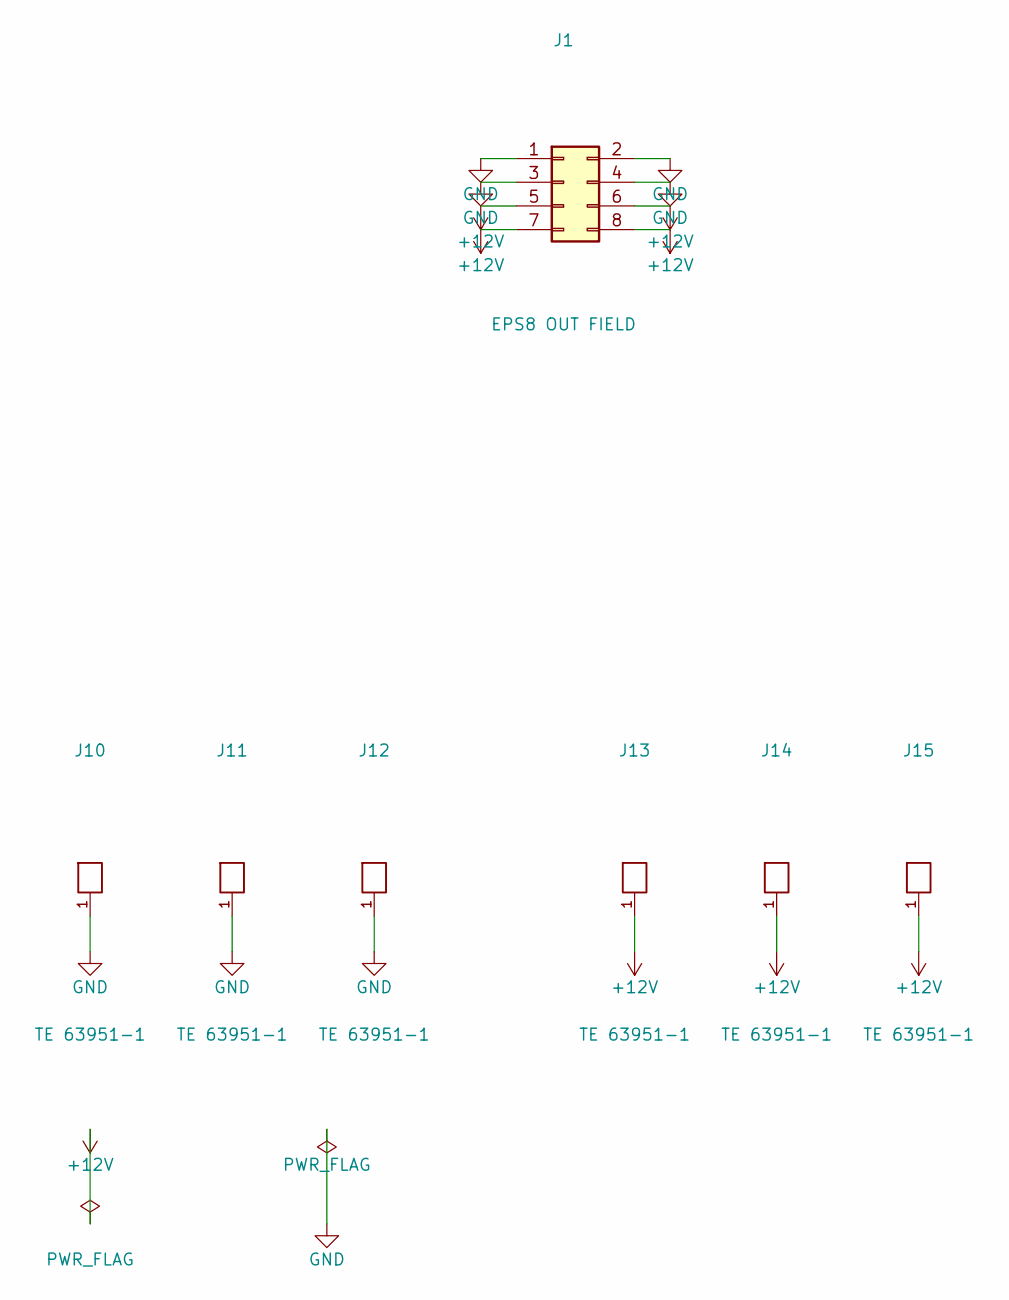
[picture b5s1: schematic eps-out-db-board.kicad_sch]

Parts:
J1: EPS8 OUT FIELD; EPS8_Daughterboard_Field_P4.20mm
J10, J11, J12, J13, J14, J15: TE 63951-1; TE_63951-1_FASTON_Tab_250x032_RA_THT; MPN 63951-1; LCSC C591344

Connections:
+12V: J1.5, J1.6, J1.7, J1.8, J13.1, J14.1, J15.1
GND: J1.1, J1.2, J1.3, J1.4, J10.1, J11.1, J12.1

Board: 4 copper layers, 8 parts (0 on the bottom side), 2 nets, no tracks yet.

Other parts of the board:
LOGO1: CEC_Logo_Copper_Small

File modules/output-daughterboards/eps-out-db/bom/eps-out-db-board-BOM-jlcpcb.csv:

"Reference","Value","Footprint","LCSC","MPN","Manufacturer"
"J1","EPS8 OUT FIELD","cec-Connector_Generic:EPS8_Daughterboard_Field_P4.20mm","","","CEC (in-house)"
"J10","TE 63951-1","cec-Connector_Blade:TE_63951-1_FASTON_Tab_250x032_RA_THT","C591344","63951-1","TE Connectivity"
"J11","TE 63951-1","cec-Connector_Blade:TE_63951-1_FASTON_Tab_250x032_RA_THT","C591344","63951-1","TE Connectivity"
"J12","TE 63951-1","cec-Connector_Blade:TE_63951-1_FASTON_Tab_250x032_RA_THT","C591344","63951-1","TE Connectivity"
"J13","TE 63951-1","cec-Connector_Blade:TE_63951-1_FASTON_Tab_250x032_RA_THT","C591344","63951-1","TE Connectivity"
"J14","TE 63951-1","cec-Connector_Blade:TE_63951-1_FASTON_Tab_250x032_RA_THT","C591344","63951-1","TE Connectivity"
"J15","TE 63951-1","cec-Connector_Blade:TE_63951-1_FASTON_Tab_250x032_RA_THT","C591344","63951-1","TE Connectivity"
